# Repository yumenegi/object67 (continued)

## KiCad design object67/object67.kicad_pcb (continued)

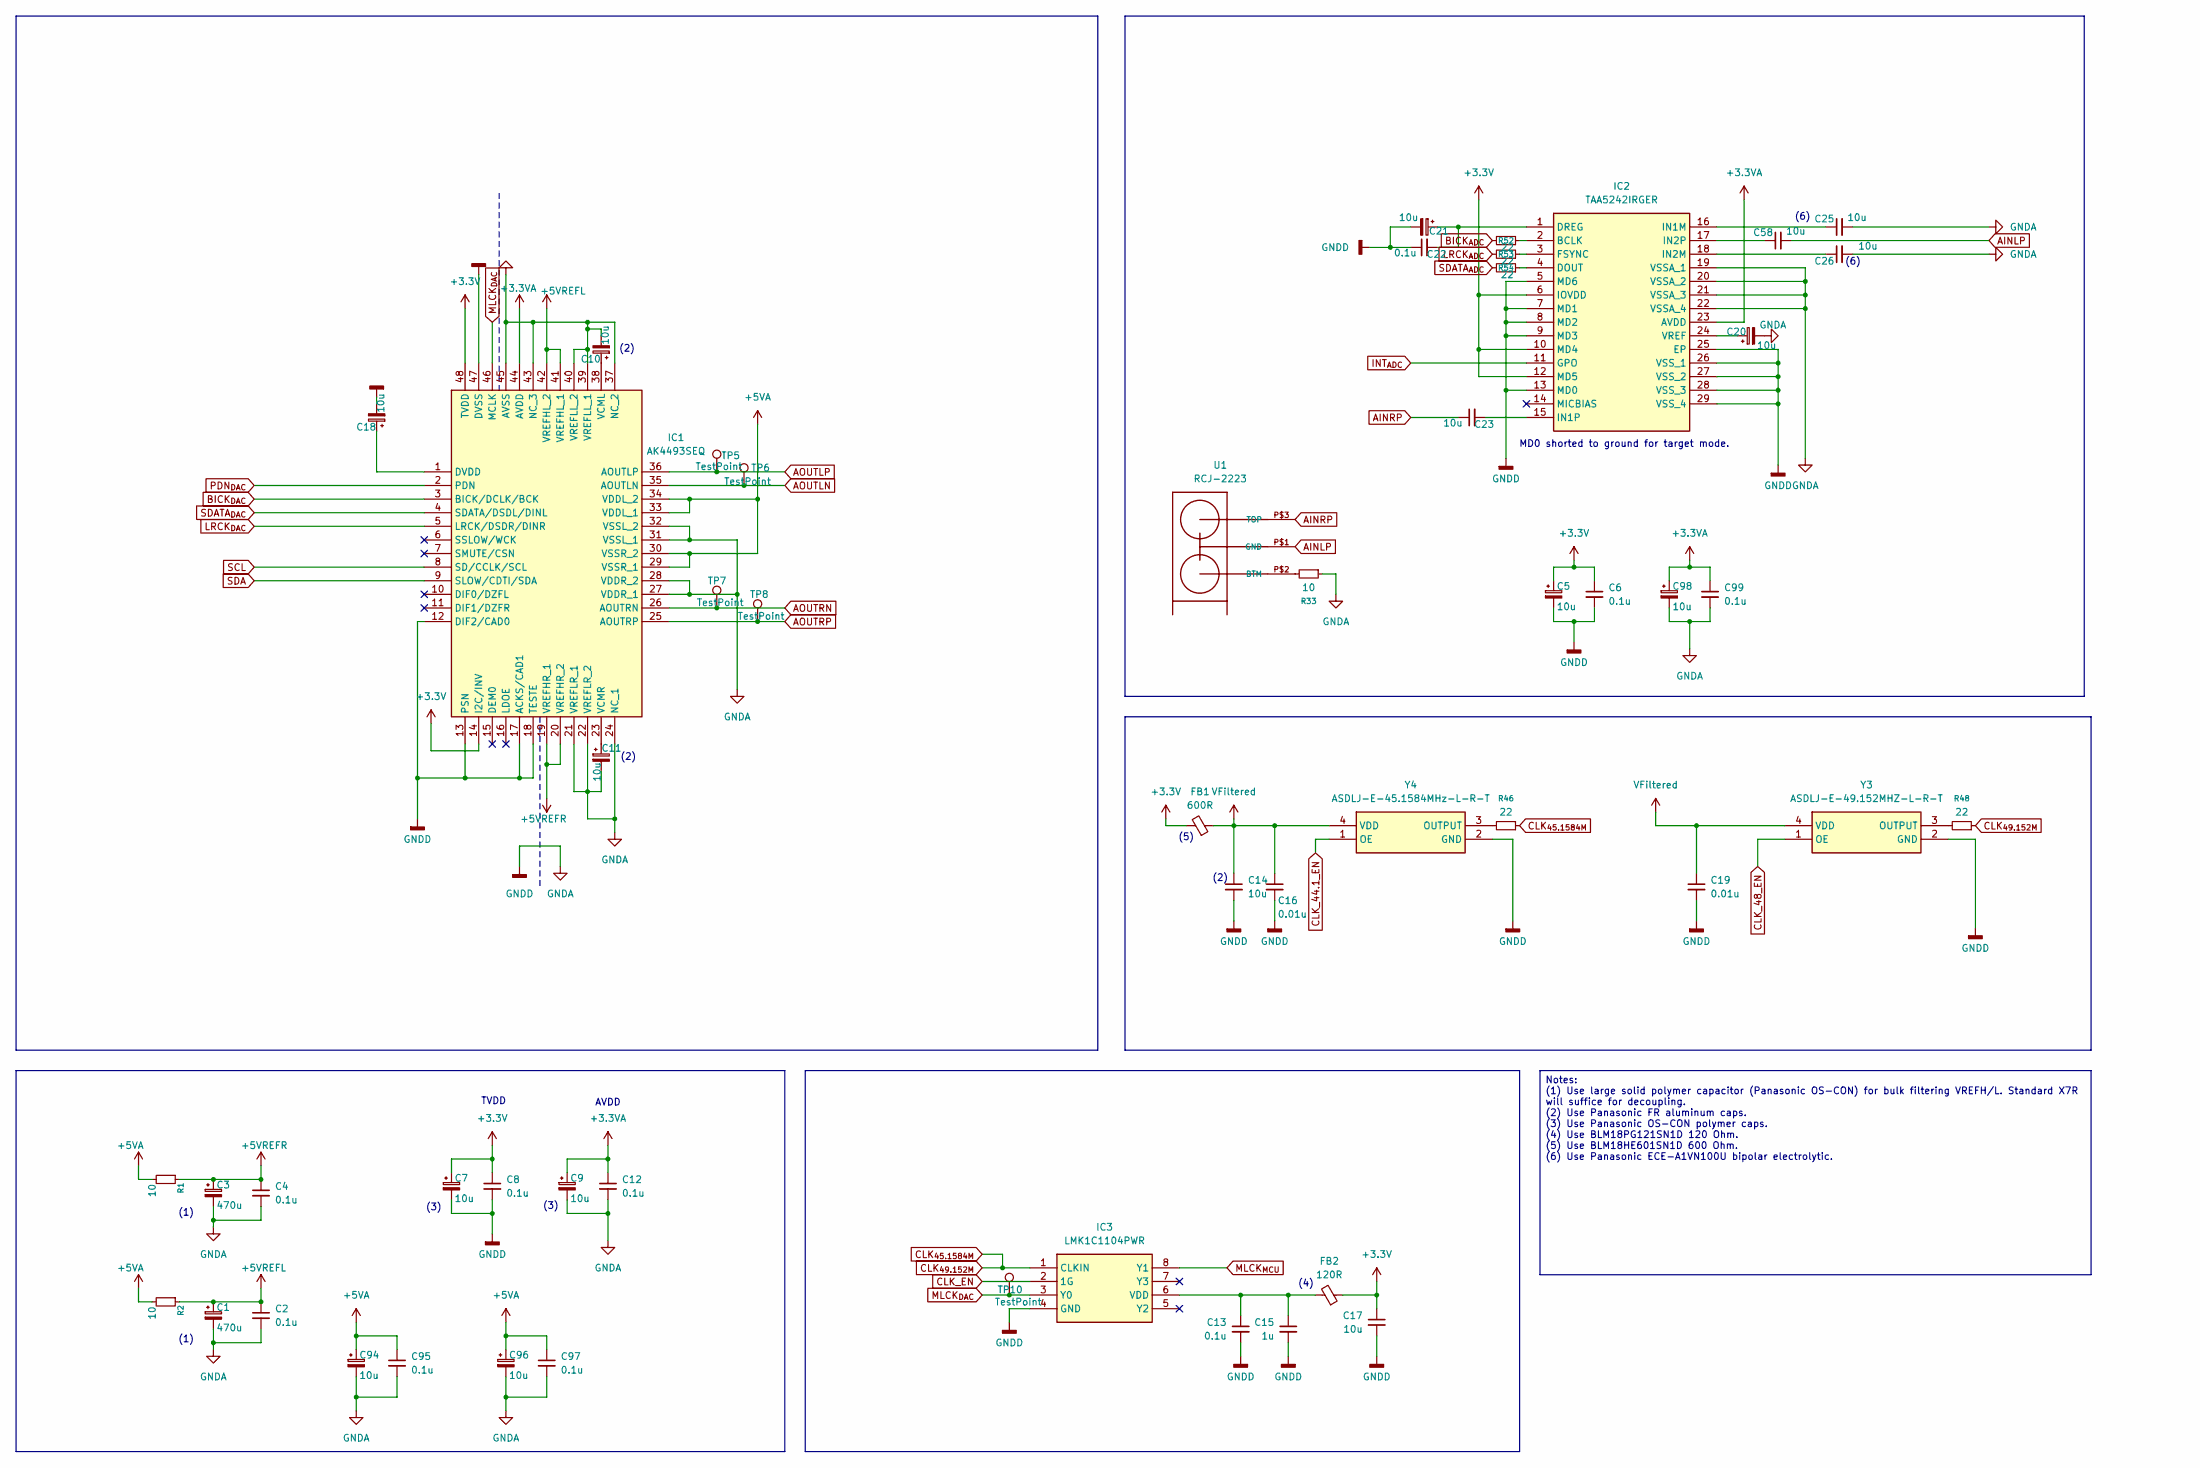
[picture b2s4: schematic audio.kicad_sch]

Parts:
C1, C3: 470u; CP_Radial_D8.0mm_P5.00mm
C2, C4, C6, C8, C12, C13, C95, C97, C99: 0.1u; C_0603_1608Metric
C5, C7, C9, C14, C18, C20, C21, C98: 10u; CP_Elec_4x5.3
C10, C11: 10u; CP_Radial_D5.0mm_P2.00mm
C15: 1u; C_1206_3216Metric
C16, C19: 0.01u; C_0402_1005Metric
C17, C23, C25, C26, C58: 10u; C_1206_3216Metric
C22: 0.1u; C_0402_1005Metric
C94, C96: 10u; CP_Elec_5x5.3
FB1: 600R; L_0603_1608Metric
FB2: 120R; L_0603_1608Metric
IC1: AK4493SEQ; LQFP-48_7x7mm_P0.5mm; Manufacturer_Part_Number AK4493SEQ; Mouser Part Number 412-AK4493SEQ
IC2: TAA5242IRGER; Manufacturer_Part_Number TAA5242IRGER
IC3: LMK1C1104PWR; TSSOP-8_4.4x3mm_P0.65mm; Manufacturer_Part_Number LMK1C1104PWR; Mouser Part Number 595-LMK1C1104PWR
R1, R2: 10; R_0402_1005Metric
R33: 10; R_1206_3216Metric
R46, R48, R52, R53, R54: 22; R_0402_1005Metric
TP5, TP6, TP7, TP8, TP10: TestPoint; TestPoint_Pad_D1.0mm
U1: RCJ-2223; DUALRCA
Y3: ASDLJ-E-49.152MHZ-L-R-T; ASDLJE49152MHZLRT; Manufacturer_Part_Number ASDLJ-E-49.152MHZ-L-R-T; Mouser Part Number 815-ASDLJE49152MHLRT
Y4: ASDLJ-E-45.1584MHz-L-R-T; ASDLJE451584MHzLRT; Manufacturer_Part_Number ASDLJ-E-45.1584MHz-L-R-T; Mouser Part Number 815-ASDLJE451584MLRT

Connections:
+3.3V: C5.1, C6.1, C7.1, C8.1, C17.1, FB1.2, FB2.1, IC1.14 (I2C/INV), IC1.48 (TVDD), IC2.6 (IOVDD), IC2.10 (MD4), IC2.12 (MD5); also elsewhere on the board
+3.3VA: C9.1, C12.1, C98.1, C99.1, IC1.44 (AVDD), IC2.23 (AVDD); also elsewhere on the board
+5VA: C94.1, C95.1, C96.1, C97.1, IC1.29 (VSSR_1), IC1.30 (VSSR_2), IC1.33 (VDDL_1), IC1.34 (VDDL_2), R1.2, R2.2; also elsewhere on the board
+5VREFL: C1.1, C2.1, IC1.41 (VREFHL_1), IC1.42 (VREFHL_2), R2.1
+5VREFR: C3.1, C4.1, IC1.19 (VREFHR_1), IC1.20 (VREFHR_2), R1.1
AINLP: C58.2, U1.P$1 (GND)
AINRP: C23.1, U1.P$3 (TOP)
AOUTLN: IC1.35 (AOUTLN), TP6.1; also elsewhere on the board
AOUTLP: IC1.36 (AOUTLP), TP5.1; also elsewhere on the board
AOUTRN: IC1.26 (AOUTRN), TP7.1; also elsewhere on the board
AOUTRP: IC1.25 (AOUTRP), TP8.1; also elsewhere on the board
BICK_{ADC}: R52.2; also elsewhere on the board
BICK_{DAC}: IC1.3 (BICK/DCLK/BCK); also elsewhere on the board
CLK_44.1_EN: Y4.1 (OE); also elsewhere on the board
CLK_48_EN: Y3.1 (OE); also elsewhere on the board
CLK_EN: IC3.2 (1G); also elsewhere on the board
CLK_{45.1584M}: IC3.1 (CLKIN), R46.1, R48.1
GND: C1.2, C2.2, C3.2, C4.2, C5.2, C6.2, C7.2, C8.2, C9.2, C10.2, C11.2, C12.2, C13.2, C14.2, C15.2, C16.2, C17.2, C18.2, C19.2, C20.2, C21.2, C22.1, C25.2, C26.2, C94.2, C95.2, C96.2, C97.2, C98.2, C99.2, IC1.12 (DIF2/CAD0), IC1.13 (PSN), IC1.17 (ACKS/CAD1), IC1.18 (TESTE), IC1.21 (VREFLR_1), IC1.22 (VREFLR_2), IC1.24 (NC_1), IC1.27 (VDDR_1), IC1.28 (VDDR_2), IC1.31 (VSSL_1), IC1.32 (VSSL_2), IC1.37 (NC_2), IC1.39 (VREFLL_1), IC1.40 (VREFLL_2), IC1.43 (NC_3), IC1.45 (AVSS), IC1.47 (DVSS), IC2.5 (MD6), IC2.7 (MD1), IC2.8 (MD2), IC2.9 (MD3), IC2.13 (MD0), IC2.19 (VSSA_1), IC2.20 (VSSA_2), IC2.21 (VSSA_3), IC2.22 (VSSA_4), IC2.25 (EP), IC2.26 (VSS_1), IC2.27 (VSS_2), IC2.28 (VSS_3), IC2.29 (VSS_4), IC3.4 (GND), R33.1, Y3.2 (GND), Y4.2 (GND); also elsewhere on the board
INT_{ADC}: IC2.11 (GPO); also elsewhere on the board
LRCK_{ADC}: R53.2; also elsewhere on the board
LRCK_{DAC}: IC1.5 (LRCK/DSDR/DINR); also elsewhere on the board
MLCK_{DAC}: IC1.46 (MCLK), IC3.3 (Y0), TP10.1
MLCK_{MCU}: IC3.8 (Y1); also elsewhere on the board
unnamed: C18.1, IC1.1 (DVDD)
unnamed: C10.1, IC1.38 (VCML)
unnamed: C11.1, IC1.23 (VCMR)
unnamed: IC2.2 (BCLK), R52.1
unnamed: IC2.4 (DOUT), R54.1
unnamed: C21.1, C22.2, IC2.1 (DREG)
unnamed: IC2.3 (FSYNC), R53.1
unnamed: C25.1, IC2.16 (IN1M)
unnamed: C23.2, IC2.15 (IN1P)
unnamed: C26.1, IC2.18 (IN2M)
unnamed: C58.1, IC2.17 (IN2P)
unnamed: C20.1, IC2.24 (VREF)
unnamed: C13.1, C15.1, FB2.2, IC3.6 (VDD)
unnamed: R33.2, U1.P$2 (BTM)
unnamed: R48.2, Y3.3 (OUTPUT)
unnamed: R46.2, Y4.3 (OUTPUT)
PDN_{DAC}: IC1.2 (PDN); also elsewhere on the board
SCL: IC1.8 (SD/CCLK/SCL); also elsewhere on the board
SDA: IC1.9 (SLOW/CDTI/SDA); also elsewhere on the board
SDATA_{ADC}: R54.2; also elsewhere on the board
SDATA_{DAC}: IC1.4 (SDATA/DSDL/DINL); also elsewhere on the board
VFiltered: C14.1, C16.1, C19.1, FB1.1, Y3.4 (VDD), Y4.4 (VDD)

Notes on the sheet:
(2)
(3)
(1)
MD0 shorted to ground for target mode.
(6)
TVDD
(4)
AVDD
(5)
Notes: (1) Use large solid polymer capacitor (Panasonic OS-CON) for bulk filtering VREFH/L. Standard X7R will suffice for decoupling. (2) Use Panasonic FR aluminum caps. (3) Use Panasonic OS-CON polymer caps. (4) Use BLM18PG121SN1D 120 Ohm. (5) Use BLM18HE601SN1D 600 Ohm. (6) Use Panasonic ECE-A1VN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

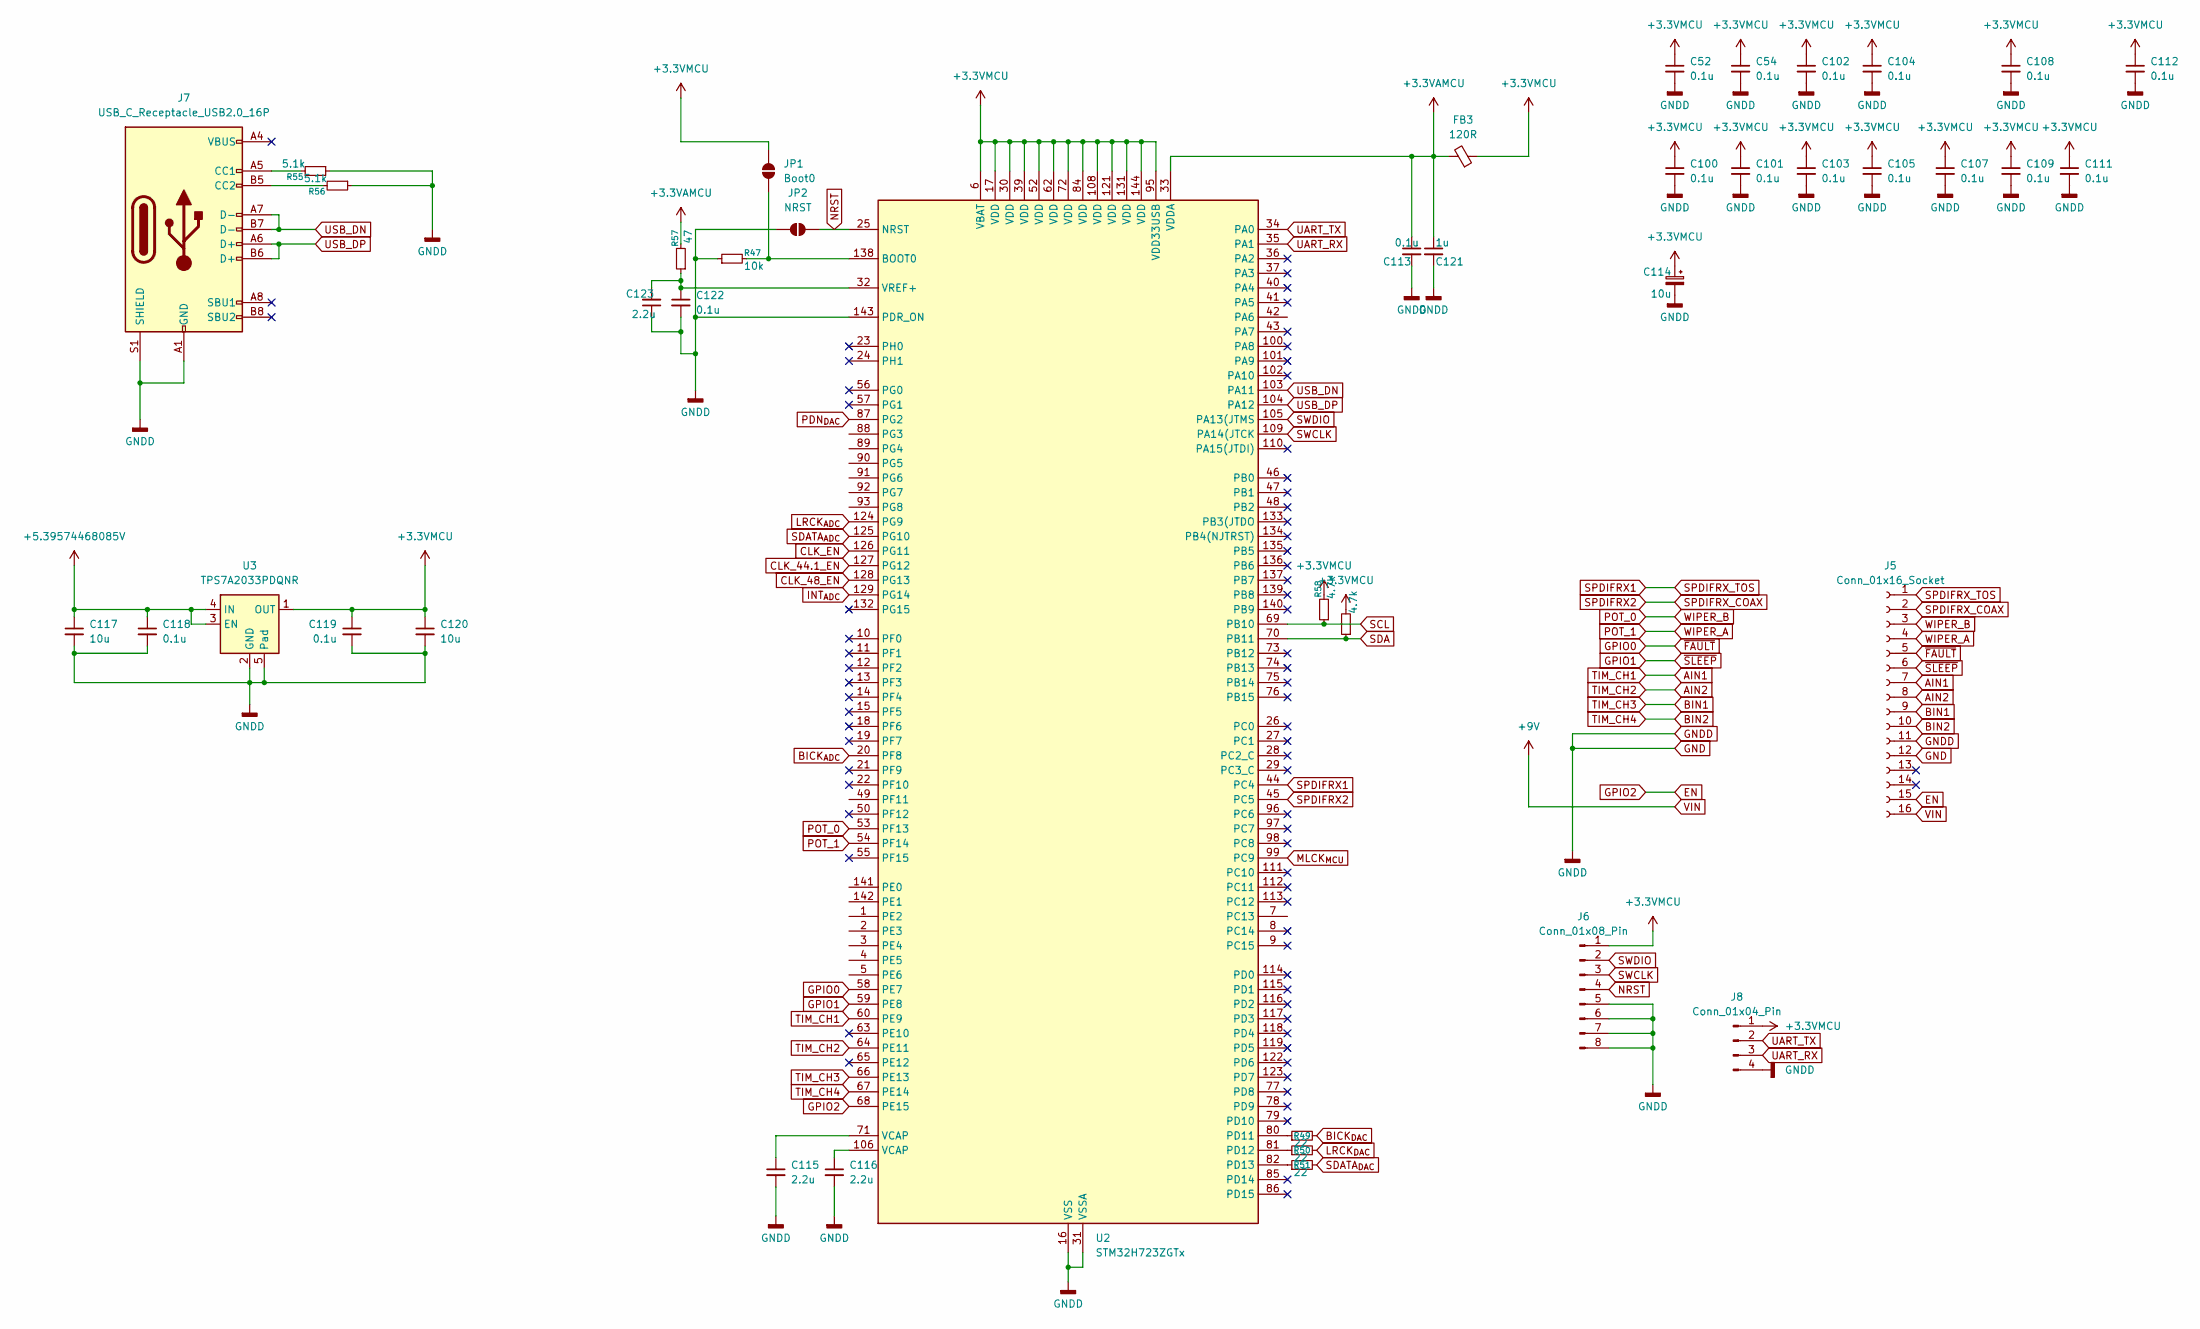
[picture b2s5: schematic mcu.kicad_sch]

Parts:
C52, C54, C100, C101, C102, C103, C104, C105, C107, C108, C109, C111, C112, C113, C122: 0.1u; C_0402_1005Metric
C114: 10u; CP_Elec_4x5.3
C115, C116, C123: 2.2u; C_0603_1608Metric
C117, C120: 10u; C_0603_1608Metric
C118, C119: 0.1u; C_0603_1608Metric
C121: 1u; C_1206_3216Metric
FB3: 120R; L_0603_1608Metric
J5: Conn_01x16_Socket; JST_PH_S16B-PH-K_1x16_P2.00mm_Horizontal
J6: Conn_01x08_Pin; PinHeader_1x08_P2.54mm_Vertical
J7: USB_C_Receptacle_USB2.0_16P; USB_C_Receptacle_GCT_USB4085
J8: Conn_01x04_Pin; PinHeader_1x04_P2.54mm_Vertical
JP1: Boot0; SolderJumper-2_P1.3mm_Open_RoundedPad1.0x1.5mm
JP2: NRST; SolderJumper-2_P1.3mm_Open_RoundedPad1.0x1.5mm
R47: 10k; R_0603_1608Metric
R49, R50, R51: 22; R_0402_1005Metric
R55, R56: 5.1k; R_0603_1608Metric
R57: 47; R_0603_1608Metric
R58, R59: 4.7k; R_0603_1608Metric
U2: STM32H723ZGTx; LQFP-144_20x20mm_P0.5mm
U3: TPS7A2033PDQNR; Texas_X2SON-4_1x1mm_P0.65mm

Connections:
+3.3VAMCU: C113.1, C121.1, FB3.2, R57.2, U2.33 (VDDA)
+3.3VMCU: C52.1, C54.1, C100.1, C101.1, C102.1, C103.1, C104.1, C105.1, C107.1, C108.1, C109.1, C111.1, C112.1, C114.1, C119.1, C120.1, FB3.1, J6.1, J8.1, JP1.2 (B), R58.2, R59.2, U2.6 (VBAT), U2.17 (VDD), U2.30 (VDD), U2.39 (VDD), U2.52 (VDD), U2.62 (VDD), U2.72 (VDD), U2.84 (VDD), U2.95 (VDD33USB), U2.108 (VDD), U2.121 (VDD), U2.131 (VDD), U2.144 (VDD), U3.1 (OUT); also elsewhere on the board
+5.39574468085V: C117.1, C118.1, U3.3 (EN), U3.4 (IN); also elsewhere on the board
AIN1: J5.7, U2.60 (PE9)
AIN2: J5.8, U2.64 (PE11)
BICK_{ADC}: U2.20 (PF8); also elsewhere on the board
BICK_{DAC}: R49.2; also elsewhere on the board
BIN1: J5.9, U2.66 (PE13)
BIN2: J5.10, U2.67 (PE14)
CLK_44.1_EN: U2.127 (PG12); also elsewhere on the board
CLK_48_EN: U2.128 (PG13); also elsewhere on the board
CLK_EN: U2.126 (PG11); also elsewhere on the board
EN: J5.15, U2.68 (PE15)
GND: C52.2, C54.2, C100.2, C101.2, C102.2, C103.2, C104.2, C105.2, C107.2, C108.2, C109.2, C111.2, C112.2, C113.2, C114.2, C115.2, C116.2, C117.2, C118.2, C119.2, C120.2, C121.2, C122.2, C123.1, J5.11, J5.12, J6.5, J6.6, J6.7, J6.8, J7.A1 (GND), J7.A12 (GND), J7.B1 (GND), J7.B12 (GND), J7.S1 (SHIELD), J8.4, JP2.1 (A), R47.1, R55.1, R56.1, U2.16 (VSS), U2.31 (VSSA), U2.38 (VSS), U2.51 (VSS), U2.61 (VSS), U2.83 (VSS), U2.94 (VSS), U2.107 (VSS), U2.120 (VSS), U2.130 (VSS), U2.143 (PDR_ON), U3.2 (GND), U3.5 (Pad); also elsewhere on the board
GPIO0: J5.5, U2.58 (PE7)
GPIO1: J5.6, U2.59 (PE8)
INT_{ADC}: U2.129 (PG14); also elsewhere on the board
LRCK_{ADC}: U2.124 (PG9); also elsewhere on the board
LRCK_{DAC}: R50.2; also elsewhere on the board
MLCK_{MCU}: U2.99 (PC9); also elsewhere on the board
NRST: J6.4, JP2.2 (B), U2.25 (NRST)
unnamed: C115.1, U2.71 (VCAP)
unnamed: C116.1, U2.106 (VCAP)
unnamed: J7.A5 (CC1), R55.2
unnamed: J7.B5 (CC2), R56.2
unnamed: JP1.1 (A), R47.2, U2.138 (BOOT0)
unnamed: R49.1, U2.80 (PD11)
unnamed: R50.1, U2.81 (PD12)
unnamed: R51.1, U2.82 (PD13)
unnamed: C122.1, C123.2, R57.1, U2.32 (VREF+)
PDN_{DAC}: U2.87 (PG2); also elsewhere on the board
POT_0: J5.3, U2.53 (PF13)
POT_1: J5.4, U2.54 (PF14)
SCL: R58.1, U2.69 (PB10); also elsewhere on the board
SDA: R59.1, U2.70 (PB11); also elsewhere on the board
SDATA_{ADC}: U2.125 (PG10); also elsewhere on the board
SDATA_{DAC}: R51.2; also elsewhere on the board
SPDIFRX1: J5.1, U2.44 (PC4)
SPDIFRX2: J5.2, U2.45 (PC5)
SWCLK: J6.3, U2.109 (PA14(JTCK)
SWDIO: J6.2, U2.105 (PA13(JTMS)
UART_RX: J8.3, U2.35 (PA1)
UART_TX: J8.2, U2.34 (PA0)
USB_DN: J7.A7 (D-), J7.B7 (D-), U2.103 (PA11)
USB_DP: J7.A6 (D+), J7.B6 (D+), U2.104 (PA12)
VIN: J5.16; also elsewhere on the board

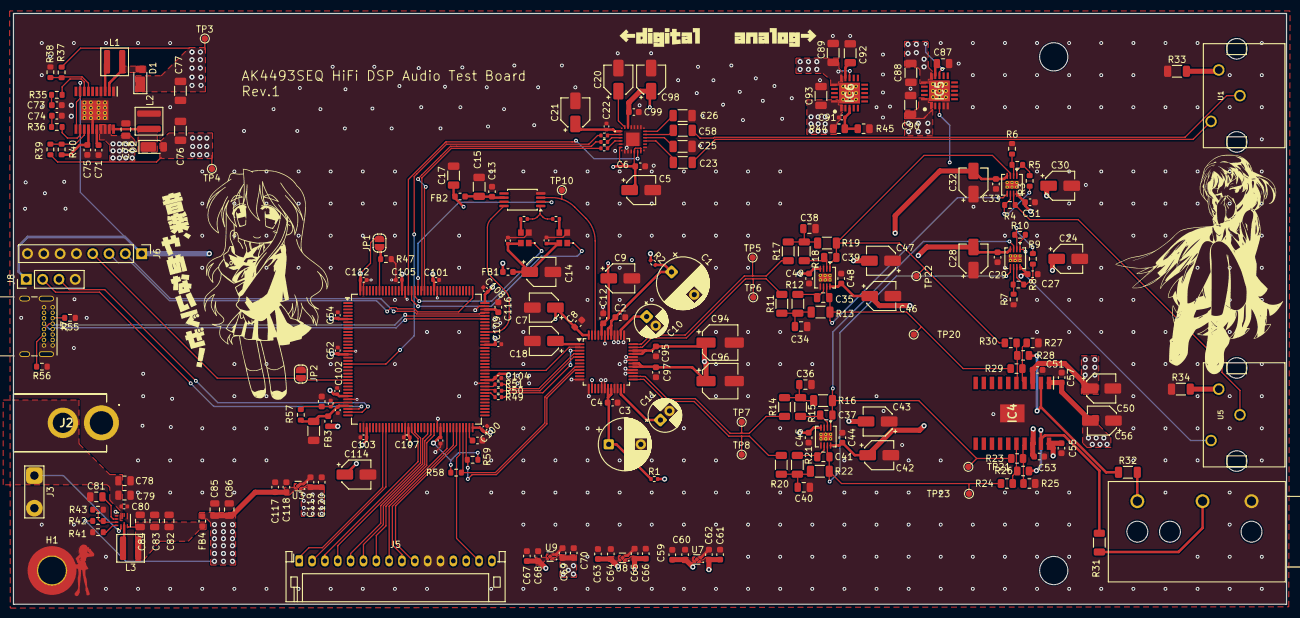
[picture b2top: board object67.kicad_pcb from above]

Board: 4 copper layers, 198.2 x 92.0 mm, 231 parts (0 on the bottom side), 128 nets.

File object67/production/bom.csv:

Designator,Footprint,Quantity,Value,LCSC Part #
"C1, C3",CP_Radial_D8.0mm_P5.00mm,2,470u,
"C10, C11",CP_Radial_D5.0mm_P2.00mm,2,10u,
"C100, C101, C102, C103, C104, C105, C107, C108, C109, C111, C112, C113, C122, C22, C52, C54",0402,16,0.1u,
"C114, C14, C18, C20, C21, C24, C28, C30, C32, C42, C43, C46, C47, C5, C50, C56, C7, C9, C98",CP_Elec_4x5.3,19,10u,
"C115, C116, C123",0603,3,2.2u,
"C117, C120, C59, C61, C63, C66, C67, C70",0603,8,10u,
"C118, C119, C12, C13, C2, C27, C29, C31, C33, C4, C44, C45, C48, C49, C51, C53, C55, C57, C6, C60, C62, C64, C65, C68, C69, C8, C95, C97, C99",0603,29,0.1u,
"C121, C15, C92",1206,3,1u,
"C16, C19",0402,2,0.01u,
"C17, C23, C25, C26, C58, C76, C77, C88, C89",1206,9,10u,
"C34, C36, C38, C40",0805,4,4.02n,
"C35, C37, C39, C41",0805,4,1n,
"C71, C75",0603,2,1u,
"C72, C78, C79",0805,3,10u,
C73,0603,1,47n,
C74,0603,1,68n,
C80,0402,1,2.2n,
C81,0805,1,470n,
"C82, C83, C84, C85, C86",0805,5,22u,
C87,0805,1,1u,
"C90, C93",1206,2,47u,
C91,0402,1,10n,
"C94, C96",CP_Elec_5x5.3,2,10u,
"D1, D2",D_PowerDI-123,2,DFLS240,
FB1,0603,1,600R,
"FB2, FB3",0603,2,120R,
FB4,0603,1,8R,
IC1,LQFP-48_7x7mm_P0.5mm,1,AK4493SEQ,
"IC10, IC7, IC8, IC9",WSON-8-1EP_3x3mm_P0.5mm_EP1.2x2mm_ThermalVias,4,OPA1612AIDRGR,
IC2,TAA5242IRGER,1,TAA5242IRGER,
IC3,TSSOP-8_4.4x3mm_P0.65mm,1,LMK1C1104PWR,
IC4,SOIC127P1040X275-21N,1,TPA6120A2DWPR,
IC5,QFN65P500X500X100-21N-D,1,TPS7A4701RGWT,
IC6,QFN65P500X500X100-21N-D,1,TPS7A3301RGWR,
J1,SWITCHCRAFT_SN37A12B,1,SN37A12B,
J2,PJ037A,1,PJ-037A,
J3,TestPoint_2Pads_Pitch5.08mm_Drill1.3mm,1,Power In,
J5,JST_PH_S16B-PH-K_1x16_P2.00mm_Horizontal,1,Conn_01x16_Socket,
J6,PinHeader_1x08_P2.54mm_Vertical,1,Conn_01x08_Pin,
J7,USB_C_Receptacle_GCT_USB4085,1,USB_C_Receptacle_USB2.0_16P,
J8,PinHeader_1x04_P2.54mm_Vertical,1,Conn_01x04_Pin,
"L1, L2",L_Wuerth_MAPI-4030,2,6.8u,
L3,L_Wuerth_MAPI-4030,1,2.2u,
"R1, R2",0402,2,10,
"R10, R3, R4, R5, R6, R7, R8, R9",0603,8,2k,
"R11, R13, R14, R16, R17, R19, R20, R22",1206,8,1.1k,
"R12, R15, R18, R21",1206,4,619,
"R23, R24, R25, R26, R27, R28, R29, R30",0805,8,1k,
"R31, R32",1206,2,39.2,
"R33, R34",1206,2,10,
R35,0603,1,12k,
R36,0603,1,15k,
R37,0603,1,2.15M,
R38,0603,1,113k,
R39,0603,1,2.1M,
R40,0603,1,100k,
R41,0603,1,7.5k,
R42,0603,1,27k,
"R43, R58, R59",0603,3,4.7k,
R44,0805,1,1.24M,
R45,0805,1,105k,
"R46, R48, R49, R50, R51, R52, R53, R54",0402,8,22,
R47,0603,1,10k,
"R55, R56",0603,2,5.1k,
R57,0603,1,47,
"TP10, TP20, TP21, TP22, TP23, TP3, TP4, TP5, TP6, TP7, TP8",TestPoint_Pad_D1.0mm,11,TestPoint,
"U1, U5",DUALRCA,2,RCJ-2223,
U10,SOP65P640X120-21N,1,ADP5070AREZ,
U11,Texas_RPU0010A_VQFN-HR-10_2x2mm_P0.5mm,1,TPS62912,
U2,LQFP-144_20x20mm_P0.5mm,1,STM32H723ZGTx,
"U3, U8, U9",Texas_X2SON-4_1x1mm_P0.65mm,3,TPS7A2033PDQNR,
U7,Texas_X2SON-4_1x1mm_P0.65mm,1,TPS7A2050PDQNR,
Y3,ASDLJE49152MHZLRT,1,ASDLJ-E-49.152MHZ-L-R-T,
Y4,ASDLJE451584MHzLRT,1,ASDLJ-E-45.1584MHz-L-R-T,

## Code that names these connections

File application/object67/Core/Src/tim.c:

/* USER CODE BEGIN Header */
/**
  ******************************************************************************
  * @file    tim.c
  * @brief   This file provides code for the configuration
  *          of the TIM instances.
  ******************************************************************************
  * @attention
  *
  * Copyright (c) 2026 STMicroelectronics.
  * All rights reserved.
  *
  * This software is licensed under terms that can be found in the LICENSE file
  * in the root directory of this software component.
  * If no LICENSE file comes with this software, it is provided AS-IS.
  *
  ******************************************************************************
  */
/* USER CODE END Header */
/* Includes ------------------------------------------------------------------*/
#include "tim.h"

/* USER CODE BEGIN 0 */

/* USER CODE END 0 */

TIM_HandleTypeDef htim1;

/* TIM1 init function */
void MX_TIM1_Init(void)
{

  /* USER CODE BEGIN TIM1_Init 0 */

  /* USER CODE END TIM1_Init 0 */

  TIM_ClockConfigTypeDef sClockSourceConfig = {0};
  TIM_MasterConfigTypeDef sMasterConfig = {0};
  TIM_OC_InitTypeDef sConfigOC = {0};
  TIM_BreakDeadTimeConfigTypeDef sBreakDeadTimeConfig = {0};

  /* USER CODE BEGIN TIM1_Init 1 */

  /* USER CODE END TIM1_Init 1 */
  htim1.Instance = TIM1;
  htim1.Init.Prescaler = 0;
  htim1.Init.CounterMode = TIM_COUNTERMODE_UP;
  htim1.Init.Period = 65535;
  htim1.Init.ClockDivision = TIM_CLOCKDIVISION_DIV1;
  htim1.Init.RepetitionCounter = 0;
  htim1.Init.AutoReloadPreload = TIM_AUTORELOAD_PRELOAD_DISABLE;
  if (HAL_TIM_Base_Init(&htim1) != HAL_OK)
  {
    Error_Handler();
  }
  sClockSourceConfig.ClockSource = TIM_CLOCKSOURCE_INTERNAL;
  if (HAL_TIM_ConfigClockSource(&htim1, &sClockSourceConfig) != HAL_OK)
  {
    Error_Handler();
  }
  if (HAL_TIM_PWM_Init(&htim1) != HAL_OK)
  {
    Error_Handler();
  }
  sMasterConfig.MasterOutputTrigger = TIM_TRGO_RESET;
  sMasterConfig.MasterOutputTrigger2 = TIM_TRGO2_RESET;
  sMasterConfig.MasterSlaveMode = TIM_MASTERSLAVEMODE_DISABLE;
  if (HAL_TIMEx_MasterConfigSynchronization(&htim1, &sMasterConfig) != HAL_OK)
  {
    Error_Handler();
  }
  sConfigOC.OCMode = TIM_OCMODE_PWM1;
  sConfigOC.Pulse = 0;
  sConfigOC.OCPolarity = TIM_OCPOLARITY_HIGH;
  sConfigOC.OCNPolarity = TIM_OCNPOLARITY_HIGH;
  sConfigOC.OCFastMode = TIM_OCFAST_DISABLE;
  sConfigOC.OCIdleState = TIM_OCIDLESTATE_RESET;
  sConfigOC.OCNIdleState = TIM_OCNIDLESTATE_RESET;
  if (HAL_TIM_PWM_ConfigChannel(&htim1, &sConfigOC, TIM_CHANNEL_1) != HAL_OK)
  {
    Error_Handler();
  }
  if (HAL_TIM_PWM_ConfigChannel(&htim1, &sConfigOC, TIM_CHANNEL_2) != HAL_OK)
  {
    Error_Handler();
  }
  if (HAL_TIM_PWM_ConfigChannel(&htim1, &sConfigOC, TIM_CHANNEL_3) != HAL_OK)
  {
    Error_Handler();
  }
  if (HAL_TIM_PWM_ConfigChannel(&htim1, &sConfigOC, TIM_CHANNEL_4) != HAL_OK)
  {
    Error_Handler();
  }
  sBreakDeadTimeConfig.OffStateRunMode = TIM_OSSR_DISABLE;
  sBreakDeadTimeConfig.OffStateIDLEMode = TIM_OSSI_DISABLE;
  sBreakDeadTimeConfig.LockLevel = TIM_LOCKLEVEL_OFF;
  sBreakDeadTimeConfig.DeadTime = 0;
  sBreakDeadTimeConfig.BreakState = TIM_BREAK_DISABLE;
  sBreakDeadTimeConfig.BreakPolarity = TIM_BREAKPOLARITY_HIGH;
  sBreakDeadTimeConfig.BreakFilter = 0;
  sBreakDeadTimeConfig.Break2State = TIM_BREAK2_DISABLE;
  sBreakDeadTimeConfig.Break2Polarity = TIM_BREAK2POLARITY_HIGH;
  sBreakDeadTimeConfig.Break2Filter = 0;
  sBreakDeadTimeConfig.AutomaticOutput = TIM_AUTOMATICOUTPUT_DISABLE;
  if (HAL_TIMEx_ConfigBreakDeadTime(&htim1, &sBreakDeadTimeConfig) != HAL_OK)
  {
    Error_Handler();
  }
  /* USER CODE BEGIN TIM1_Init 2 */

  /* USER CODE END TIM1_Init 2 */
  HAL_TIM_MspPostInit(&htim1);

}

void HAL_TIM_Base_MspInit(TIM_HandleTypeDef* tim_baseHandle)
{

  if(tim_baseHandle->Instance==TIM1)
  {
  /* USER CODE BEGIN TIM1_MspInit 0 */

  /* USER CODE END TIM1_MspInit 0 */
    /* TIM1 clock enable */
    __HAL_RCC_TIM1_CLK_ENABLE();
  /* USER CODE BEGIN TIM1_MspInit 1 */

  /* USER CODE END TIM1_MspInit 1 */
  }
}
void HAL_TIM_MspPostInit(TIM_HandleTypeDef* timHandle)
{

  GPIO_InitTypeDef GPIO_InitStruct = {0};
  if(timHandle->Instance==TIM1)
  {
  /* USER CODE BEGIN TIM1_MspPostInit 0 */

  /* USER CODE END TIM1_MspPostInit 0 */

    __HAL_RCC_GPIOE_CLK_ENABLE();
    /**TIM1 GPIO Configuration
    PE9     ------> TIM1_CH1
    PE11     ------> TIM1_CH2
    PE13     ------> TIM1_CH3
    PE14     ------> TIM1_CH4
    */
    GPIO_InitStruct.Pin = GPIO_PIN_9|GPIO_PIN_11|GPIO_PIN_13|GPIO_PIN_14;
    GPIO_InitStruct.Mode = GPIO_MODE_AF_PP;
    GPIO_InitStruct.Pull = GPIO_NOPULL;
    GPIO_InitStruct.Speed = GPIO_SPEED_FREQ_LOW;
    GPIO_InitStruct.Alternate = GPIO_AF1_TIM1;
    HAL_GPIO_Init(GPIOE, &GPIO_InitStruct);

  /* USER CODE BEGIN TIM1_MspPostInit 1 */

  /* USER CODE END TIM1_MspPostInit 1 */
  }

}

void HAL_TIM_Base_MspDeInit(TIM_HandleTypeDef* tim_baseHandle)
{

  if(tim_baseHandle->Instance==TIM1)
  {
  /* USER CODE BEGIN TIM1_MspDeInit 0 */

  /* USER CODE END TIM1_MspDeInit 0 */
    /* Peripheral clock disable */
    __HAL_RCC_TIM1_CLK_DISABLE();
  /* USER CODE BEGIN TIM1_MspDeInit 1 */

  /* USER CODE END TIM1_MspDeInit 1 */
  }
}

/* USER CODE BEGIN 1 */

/* USER CODE END 1 */

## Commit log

2026-02-06 Added datasheets and kicad project
2026-02-10 Added motor_board KiCad Project
2026-02-11 Added TODO for motor_board
2026-02-11 Created subpages
2026-02-11 Minor chanages
2026-02-12 Finished schematic for DAC
2026-02-16 Finished motor_board & added SPDIF
2026-02-23 Began motor board layour
2026-02-24 Finished motor board PCB
2026-02-24 Analog frontend
2026-02-24 Front end complete
2026-02-24 KiCad crashed
2026-02-24 KiCad crashed x2
2026-02-24 Update feedback resistor value
2026-02-24 Switching power supply
2026-03-02 Added application
2026-03-03 そうじしました
2026-03-07 Add LDO
2026-03-07 Updated models
2026-03-07 Finished layout
2026-03-09 Start layout
2026-03-09 Updated pcb
2026-03-09 More layouts
2026-03-09 Layout for ADP5070
2026-03-09 Finished layout for ADC DAC, starting filter
2026-03-09 Filter
2026-03-09 Updated IOC file
2026-03-10 Finished layout, start MCU
2026-03-12 LAyout
2026-03-12 Test via stitching
2026-03-12 Skibidi
2026-03-12 done
2026-03-22 Modified motor_board; larger DC/DC inductor
2026-03-30 six seven
